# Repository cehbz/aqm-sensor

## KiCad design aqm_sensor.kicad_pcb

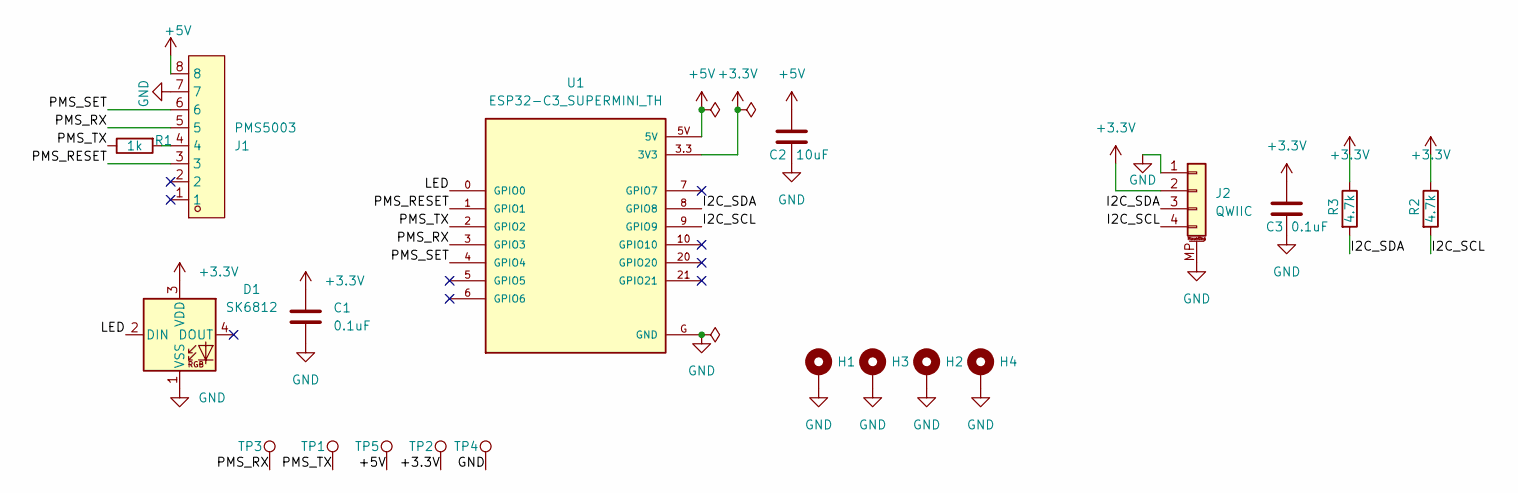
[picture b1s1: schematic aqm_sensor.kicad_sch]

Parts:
C1, C3: 0.1uF; C_1206_3216Metric
C2: 10uF; C_0805_2012Metric
D1: SK6812; LED_SK6812_PLCC4_5.0x5.0mm_P3.2mm
H1, H2, H3, H4: MountingHole_2.7mm_M2.5_Pad_Via
J1: PMS5003; CONN-TH_8P-P1.25_HCTL_HC-1.25-8AW; LCSC Part C2845541
J2: QWIIC; JST_SH_SM04B-SRSS-TB_1x04-1MP_P1.00mm_Horizontal
R1: 1k; R_1206_3216Metric
R2, R3: 4.7k; R_1206_3216Metric
TP1: TX; TestPoint_Loop_D2.50mm_Drill1.0mm
TP2: 3.3V; TestPoint_Pad_D1.5mm
TP3: RX; TestPoint_Loop_D2.50mm_Drill1.0mm
TP4: GND; TestPoint_Pad_D1.5mm
TP5: 5V; TestPoint_Pad_D1.5mm
U1: ESP32-C3_SUPERMINI_TH; MODULE_ESP32-C3_SUPERMINI_TH

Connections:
+3.3V: C1.2, C3.2, D1.3 (VDD), J2.2, R2.1, R3.1, TP2.1, U1.3.3 (3V3)
+5V: C2.1, J1.8, TP5.1, U1.5V
/I2C_SCL: J2.4, R2.2, U1.9 (GPIO9)
/I2C_SDA: J2.3, R3.2, U1.8 (GPIO8)
/LED: D1.2 (DIN), U1.0 (GPIO0)
/PMS_RESET: J1.3, U1.1 (GPIO1)
/PMS_RX: J1.5, TP3.1, U1.3 (GPIO3)
/PMS_SET: J1.6, U1.4 (GPIO4)
/PMS_TX: R1.1, TP1.1, U1.2 (GPIO2)
GND: C1.1, C2.2, C3.1, D1.1 (VSS), H1.1, H2.1, H3.1, H4.1, J1.7, J2.1, J2.MP (MountPin), TP4.1, U1.G (GND)
unnamed: J1.4, R1.2

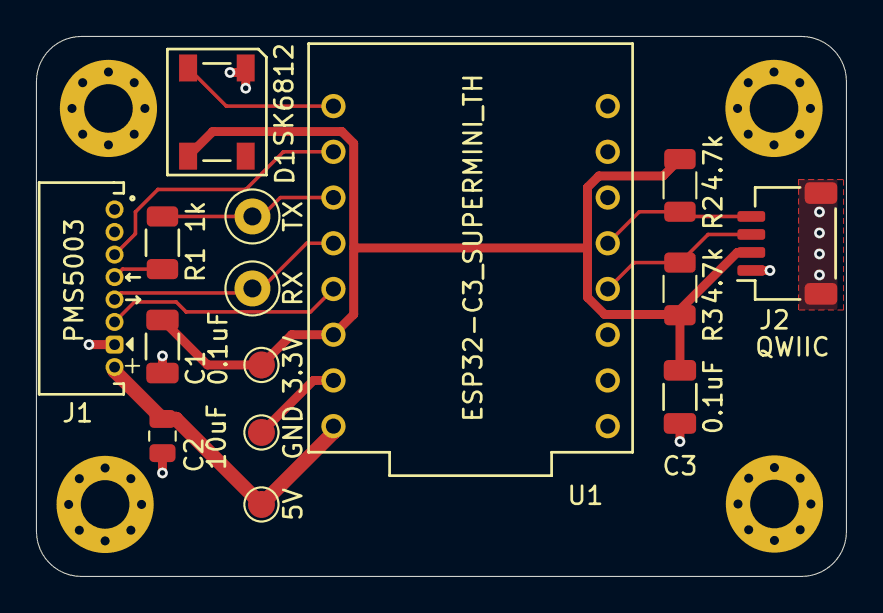
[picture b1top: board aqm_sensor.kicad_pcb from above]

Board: 2 copper layers, 45.0 x 30.0 mm, 19 parts (0 on the bottom side), 11 nets.

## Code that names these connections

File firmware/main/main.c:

#include <stdio.h>
#include <string.h>
#include "freertos/FreeRTOS.h"
#include "freertos/task.h"
#include "esp_log.h"
#include "driver/gpio.h"
#include "driver/uart.h"
#include "led_strip.h"

static const char *TAG = "pms5003";

#define LED_GPIO        0
#define LED_COUNT       1
#define BRIGHTNESS      40

#define PMS_SET_GPIO    1
#define PMS_RESET_GPIO  4

#define PMS_UART        UART_NUM_1
#define PMS_BAUD        9600
#define PMS_FRAME_LEN   32
#define PMS_BUF_SIZE    256

static led_strip_handle_t s_strip = NULL;

static void set_led(uint8_t r, uint8_t g, uint8_t b)
{
    if (s_strip) {
        led_strip_set_pixel(s_strip, 0, r, g, b);
        led_strip_refresh(s_strip);
    }
}

static void init_led(void)
{
    led_strip_config_t cfg = {
        .strip_gpio_num = LED_GPIO,
        .max_leds = LED_COUNT,
        .led_model = LED_MODEL_WS2812,
        .color_component_format = LED_STRIP_COLOR_COMPONENT_FMT_GRB,
        .flags.invert_out = false,
    };
    led_strip_rmt_config_t rmt = {
        .clk_src = RMT_CLK_SRC_DEFAULT,
        .resolution_hz = 0,
        .mem_block_symbols = 0,
        .flags.with_dma = false,
    };
    ESP_ERROR_CHECK(led_strip_new_rmt_device(&cfg, &rmt, &s_strip));
    led_strip_clear(s_strip);
    led_strip_refresh(s_strip);
}

static void init_pms_control(void)
{
    gpio_config_t io = {
        .pin_bit_mask = (1ULL << PMS_SET_GPIO) | (1ULL << PMS_RESET_GPIO),
        .mode = GPIO_MODE_OUTPUT,
    };
    gpio_config(&io);

    gpio_set_level(PMS_SET_GPIO, 1);
    gpio_set_level(PMS_RESET_GPIO, 0);
    vTaskDelay(pdMS_TO_TICKS(100));
    gpio_set_level(PMS_RESET_GPIO, 1);
    vTaskDelay(pdMS_TO_TICKS(1000));
    ESP_LOGI(TAG, "PMS5003 SET=high, RESET released");
}

static void try_uart_on_gpio(int rx_gpio)
{
    // Uninstall previous driver if any
    uart_driver_delete(PMS_UART);

    uart_config_t uart_cfg = {
        .baud_rate = PMS_BAUD,
        .data_bits = UART_DATA_8_BITS,
        .parity = UART_PARITY_DISABLE,
        .stop_bits = UART_STOP_BITS_1,
        .flow_ctrl = UART_HW_FLOWCTRL_DISABLE,
    };
    ESP_ERROR_CHECK(uart_param_config(PMS_UART, &uart_cfg));
    ESP_ERROR_CHECK(uart_set_pin(PMS_UART,
        UART_PIN_NO_CHANGE, rx_gpio,
        UART_PIN_NO_CHANGE, UART_PIN_NO_CHANGE));
    ESP_ERROR_CHECK(uart_driver_install(PMS_UART, PMS_BUF_SIZE, 0, 0, NULL, 0));

    ESP_LOGW(TAG, "=== Listening on GPIO%d for 10 seconds ===", rx_gpio);

    uint8_t buf[PMS_BUF_SIZE];
    for (int attempt = 0; attempt < 5; attempt++) {
        int bytes = uart_read_bytes(PMS_UART, buf, PMS_BUF_SIZE,
                                    pdMS_TO_TICKS(2000));
        if (bytes > 0) {
            ESP_LOGI(TAG, "GPIO%d: got %d bytes!", rx_gpio, bytes);
            // Dump first 32 bytes as hex
            char hex[97];
            int pos = 0;
            for (int i = 0; i < bytes && i < 32; i++)
                pos += snprintf(hex + pos, sizeof(hex) - pos, "%02x ", buf[i]);
            ESP_LOGI(TAG, "  raw: %s", hex);

            // Check for PMS start bytes
            for (int i = 0; i < bytes - 1; i++) {
                if (buf[i] == 0x42 && buf[i + 1] == 0x4D) {
                    ESP_LOGI(TAG, "  Found PMS5003 frame header at offset %d!", i);
                    return;
                }
            }
        } else {
            ESP_LOGW(TAG, "GPIO%d: timeout (attempt %d/5)", rx_gpio, attempt + 1);
        }
    }
}

static bool parse_pms_frame(const uint8_t *buf, int len)
{
    for (int i = 0; i <= len - PMS_FRAME_LEN; i++) {
        if (buf[i] != 0x42 || buf[i + 1] != 0x4D)
            continue;

        uint16_t frame_len = (buf[i + 2] << 8) | buf[i + 3];
        if (frame_len != 28)
            continue;

        uint16_t checksum = 0;
        for (int j = 0; j < PMS_FRAME_LEN - 2; j++)
            checksum += buf[i + j];

        uint16_t expected = (buf[i + 30] << 8) | buf[i + 31];
        if (checksum != expected) {
            ESP_LOGW(TAG, "Checksum mismatch: calc=%04x expected=%04x", checksum, expected);
            continue;
        }

        uint16_t pm1_atm  = (buf[i + 10] << 8) | buf[i + 11];
        uint16_t pm25_atm = (buf[i + 12] << 8) | buf[i + 13];
        uint16_t pm10_atm = (buf[i + 14] << 8) | buf[i + 15];

        uint16_t cnt_03 = (buf[i + 16] << 8) | buf[i + 17];
        uint16_t cnt_05 = (buf[i + 18] << 8) | buf[i + 19];
        uint16_t cnt_10 = (buf[i + 20] << 8) | buf[i + 21];
        uint16_t cnt_25 = (buf[i + 22] << 8) | buf[i + 23];

        ESP_LOGI(TAG, "PM1.0: %u  PM2.5: %u  PM10: %u ug/m3",
                 pm1_atm, pm25_atm, pm10_atm);
        ESP_LOGI(TAG, ">0.3um: %u  >0.5um: %u  >1.0um: %u  >2.5um: %u",
                 cnt_03, cnt_05, cnt_10, cnt_25);
        return true;
    }
    return false;
}

void app_main(void)
{
    init_led();
    set_led(0, 0, BRIGHTNESS);
    ESP_LOGI(TAG, "PMS5003 UART probe starting...");

    init_pms_control();

    // Try GPIO3 first (expected pin based on schematic)
    set_led(BRIGHTNESS, 0, BRIGHTNESS);  // purple = trying GPIO3
    try_uart_on_gpio(3);

    // Try GPIO2 as well (in case nets are swapped)
    set_led(0, BRIGHTNESS, BRIGHTNESS);  // cyan = trying GPIO2
    try_uart_on_gpio(2);

    // Now settle on GPIO3 for continuous reading
    ESP_LOGW(TAG, "=== Continuous read on GPIO3 ===");
    uart_driver_delete(PMS_UART);
    uart_config_t uart_cfg = {
        .baud_rate = PMS_BAUD,
        .data_bits = UART_DATA_8_BITS,
        .parity = UART_PARITY_DISABLE,
        .stop_bits = UART_STOP_BITS_1,
        .flow_ctrl = UART_HW_FLOWCTRL_DISABLE,
    };
    uart_param_config(PMS_UART, &uart_cfg);
    uart_set_pin(PMS_UART, UART_PIN_NO_CHANGE, 3,
                 UART_PIN_NO_CHANGE, UART_PIN_NO_CHANGE);
    uart_driver_install(PMS_UART, PMS_BUF_SIZE, 0, 0, NULL, 0);

    set_led(BRIGHTNESS, BRIGHTNESS, 0);  // yellow = waiting
    uint8_t buf[PMS_BUF_SIZE];

    while (1) {
        int bytes = uart_read_bytes(PMS_UART, buf, PMS_BUF_SIZE,
                                    pdMS_TO_TICKS(3000));
        if (bytes > 0 && parse_pms_frame(buf, bytes)) {
            set_led(0, BRIGHTNESS, 0);  // green
        } else if (bytes > 0) {
            char hex[97];
            int pos = 0;
            for (int i = 0; i < bytes && i < 32; i++)
                pos += snprintf(hex + pos, sizeof(hex) - pos, "%02x ", buf[i]);
            ESP_LOGW(TAG, "Got %d bytes, no valid frame: %s", bytes, hex);
        }
        vTaskDelay(pdMS_TO_TICKS(1000));
    }
}
